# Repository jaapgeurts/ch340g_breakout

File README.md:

# ch340g_breakout
CH340G USB to Serial breakout board

Simple breakout board with oscillator

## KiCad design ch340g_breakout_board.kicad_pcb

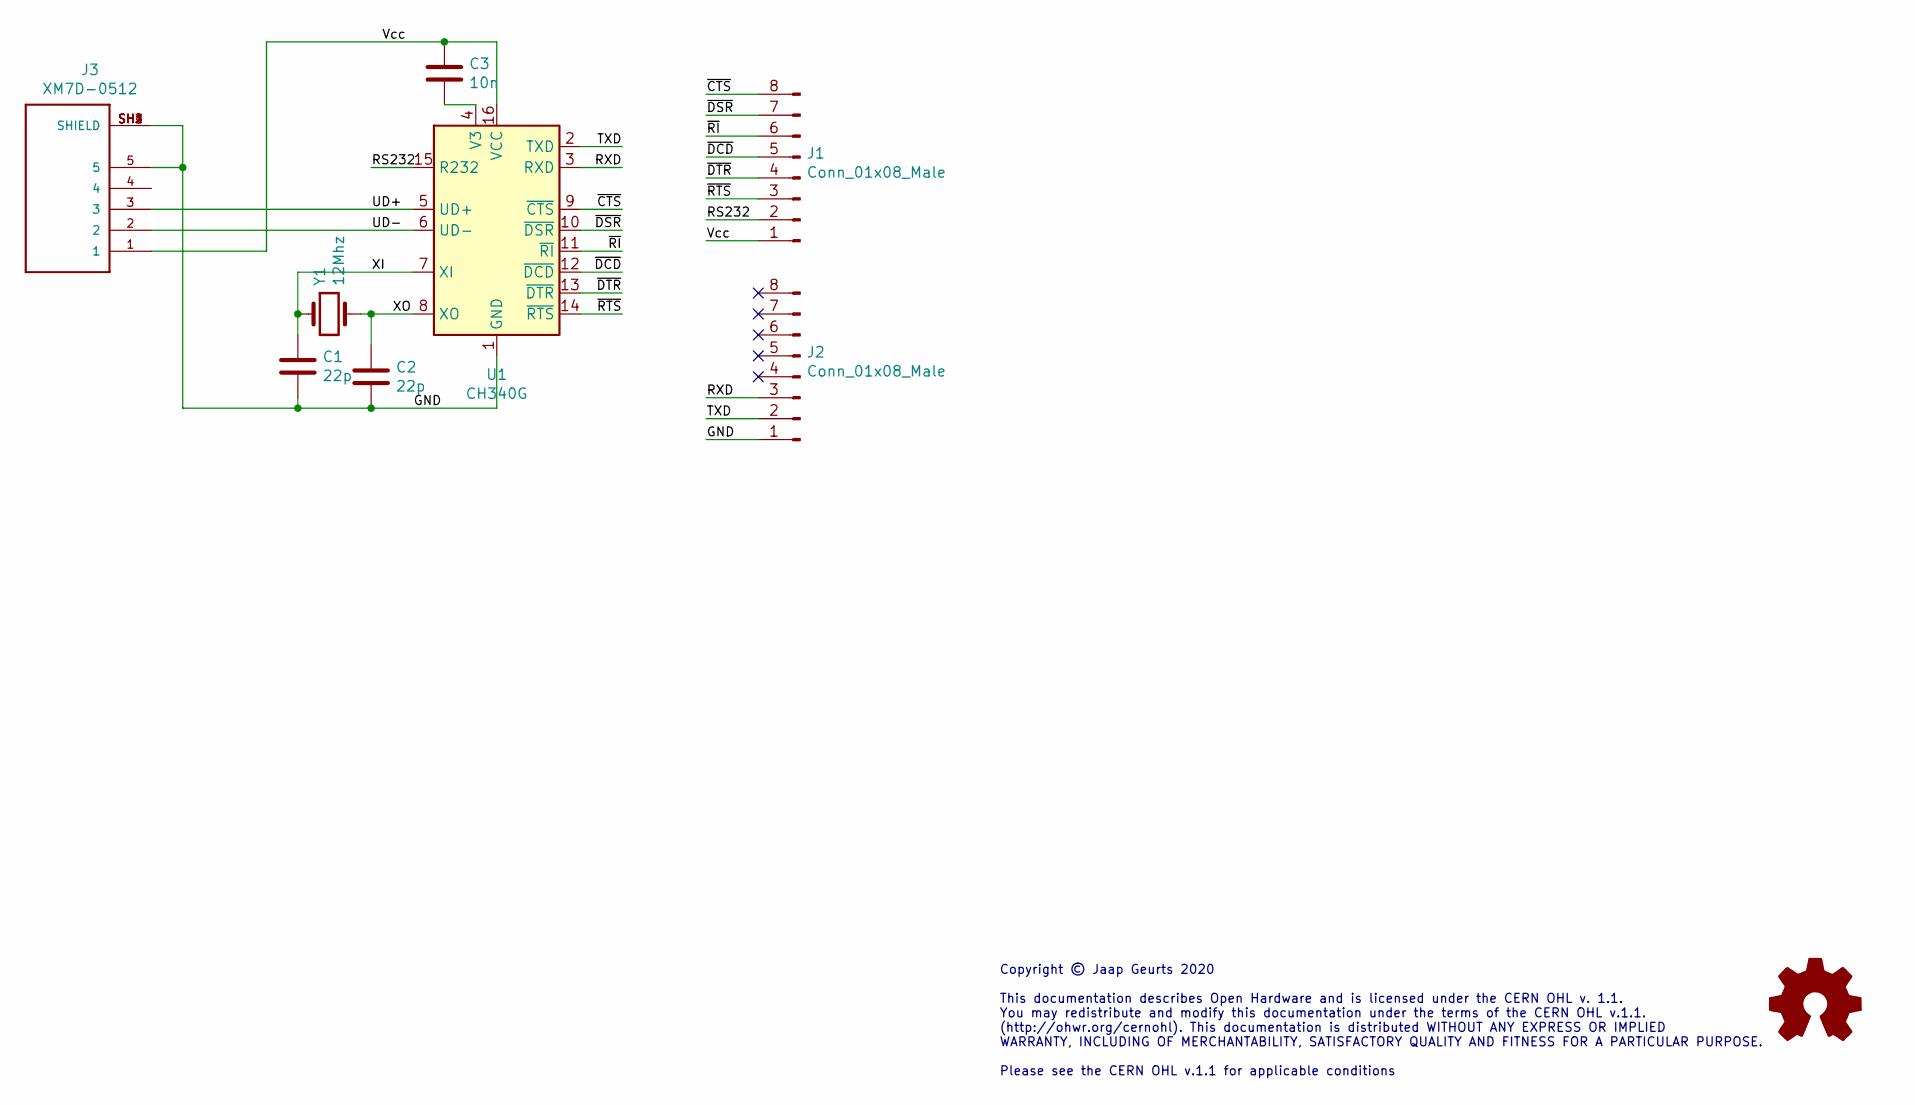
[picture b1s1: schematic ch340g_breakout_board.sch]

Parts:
C1, C2: 22p; C_Disc_D3.0mm_W1.6mm_P2.50mm
C3: 10n; C_Disc_D3.0mm_W1.6mm_P2.50mm
J1, J2: Conn_01x08_Male; PinHeader_1x08_P2.54mm_Vertical
J3: XM7D-0512; OMRON_XM7D-0512
U1: CH340G; SOIC-16_3.9x9.9mm_P1.27mm
Y1: 12Mhz; Crystal_HC49-U_Vertical

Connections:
/GND: C1.2, C2.2, J2.1, J3.5, J3.SH1 (SHIELD), J3.SH2 (SHIELD), J3.SH3 (SHIELD), J3.SH4 (SHIELD), U1.1 (GND)
/RS232: J1.2, U1.15 (R232)
/RXD: J2.3, U1.3 (RXD)
/TXD: J2.2, U1.2 (TXD)
/UD+: J3.3, U1.5 (UD+)
/UD-: J3.2, U1.6 (UD-)
/Vcc: C3.1, J1.1, J3.1, U1.16 (VCC)
/XI: C1.1, U1.7 (XI), Y1.1
/XO: C2.1, U1.8 (XO), Y1.2
/~CTS: J1.8, U1.9 (~CTS)
/~DCD: J1.5, U1.12 (~DCD)
/~DSR: J1.7, U1.10 (~DSR)
/~DTR: J1.4, U1.13 (~DTR)
/~RI: J1.6, U1.11 (~RI)
/~RTS: J1.3, U1.14 (~RTS)
unnamed: C3.2, U1.4 (V3)

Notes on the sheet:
Copyright © Jaap Geurts 2020 This documentation describes Open Hardware and is licensed under the CERN OHL v. 1.1. You may redistribute and modify this documentation under the terms of the CERN OHL v.1.1. (http://ohwr.org/cernohl). This documentation is distributed WITHOUT ANY EXPRESS OR IMPLIED WA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

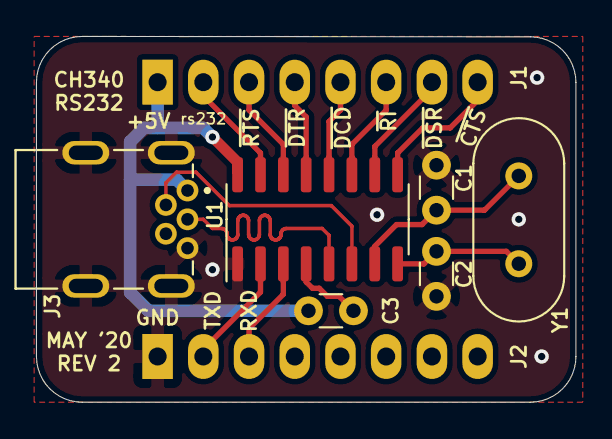
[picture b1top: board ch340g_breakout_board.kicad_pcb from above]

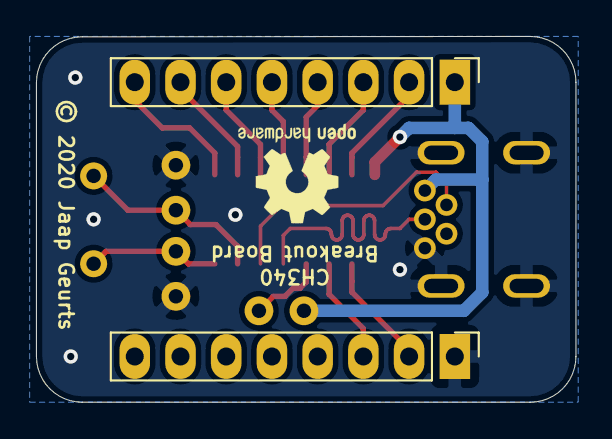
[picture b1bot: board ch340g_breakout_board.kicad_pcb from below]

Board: 2 copper layers, 30.0 x 20.3 mm, 8 parts (2 on the bottom side), 16 nets.

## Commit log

2020-03-11 Improved layout
2020-03-11 Renamed project
2020-03-11 Added license
2020-05-09 Updated to REV2: Includes USB-Mini B connector
2020-05-16 Revision 2

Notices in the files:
ch340g_breakout_board.kicad_pcb:
© 2020 Jaap Geurts
